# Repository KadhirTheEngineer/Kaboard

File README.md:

# Kaboard

An ultra-low profile 36-key wireless split keyboard with the Seeed XIAO nrf52840 dev board. Low power and insane battery life. 

Based on the chocofi and wireless corne.

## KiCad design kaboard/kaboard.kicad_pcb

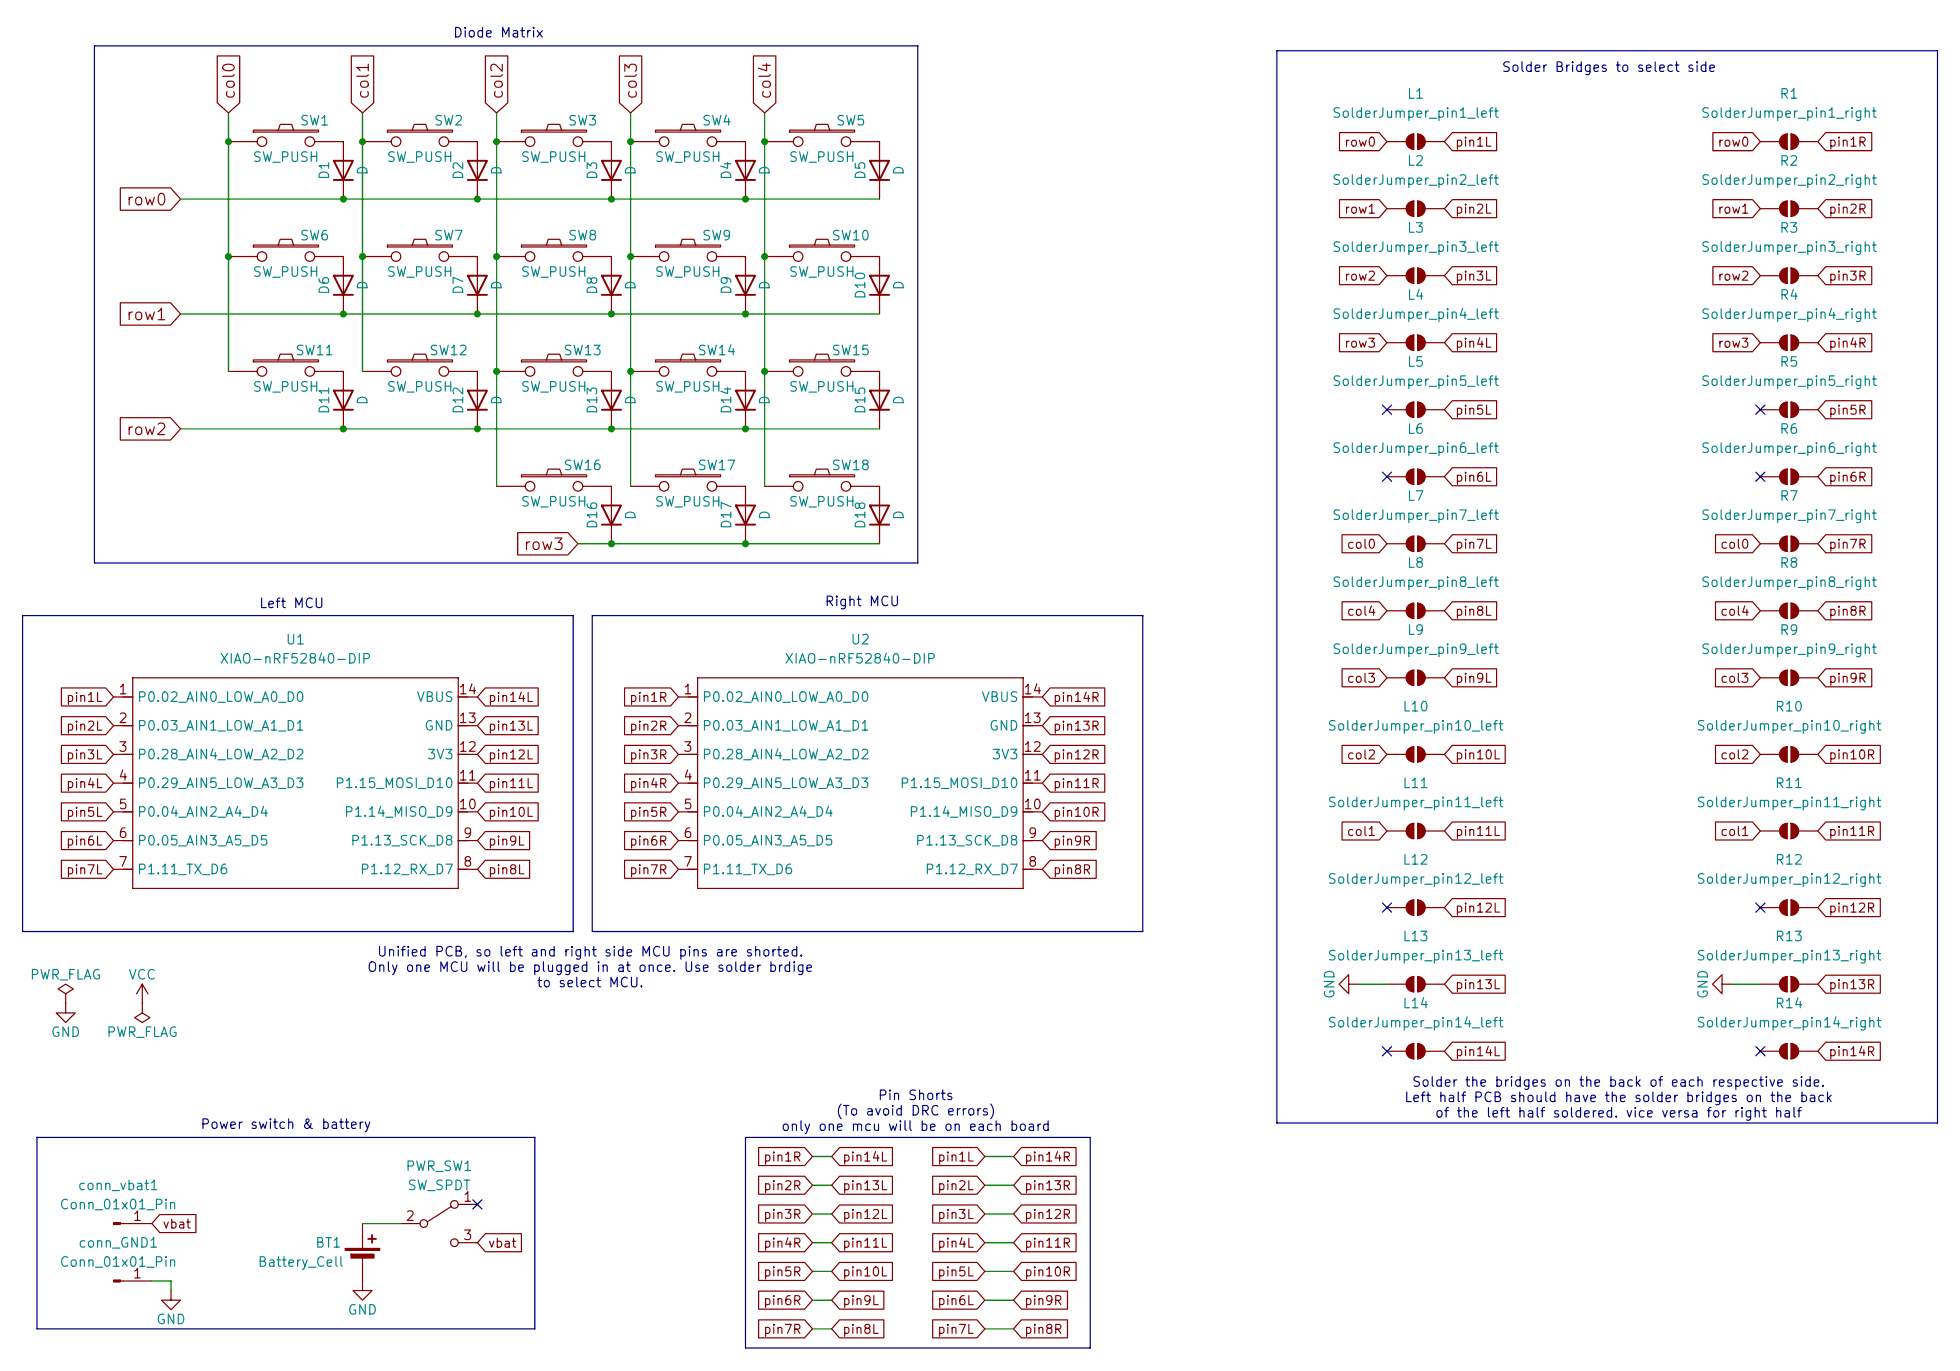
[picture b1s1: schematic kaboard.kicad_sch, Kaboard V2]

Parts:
BT1: Battery_Cell; Battery_pads_reversible
D1, D2, D3, D4, D5, D6, D7, D8, D9, D10, D11, D12, D13, D14, D15, D16, D17, D18: D; D_SMD_TH
L1: SolderJumper_pin1_left; SolderJumper-2_P1.3mm_Open_TrianglePad1.0x1.5mm
L2: SolderJumper_pin2_left; SolderJumper-2_P1.3mm_Open_TrianglePad1.0x1.5mm
L3: SolderJumper_pin3_left; SolderJumper-2_P1.3mm_Open_TrianglePad1.0x1.5mm
L4: SolderJumper_pin4_left; SolderJumper-2_P1.3mm_Open_TrianglePad1.0x1.5mm
L5: SolderJumper_pin5_left; SolderJumper-2_P1.3mm_Open_TrianglePad1.0x1.5mm
L6: SolderJumper_pin6_left; SolderJumper-2_P1.3mm_Open_TrianglePad1.0x1.5mm
L7: SolderJumper_pin7_left; SolderJumper-2_P1.3mm_Open_TrianglePad1.0x1.5mm
L8: SolderJumper_pin8_left; SolderJumper-2_P1.3mm_Open_TrianglePad1.0x1.5mm
L9: SolderJumper_pin9_left; SolderJumper-2_P1.3mm_Open_TrianglePad1.0x1.5mm
L10: SolderJumper_pin10_left; SolderJumper-2_P1.3mm_Open_TrianglePad1.0x1.5mm
L11: SolderJumper_pin11_left; SolderJumper-2_P1.3mm_Open_TrianglePad1.0x1.5mm
L12: SolderJumper_pin12_left; SolderJumper-2_P1.3mm_Open_TrianglePad1.0x1.5mm
L13: SolderJumper_pin13_left; SolderJumper-2_P1.3mm_Open_TrianglePad1.0x1.5mm
L14: SolderJumper_pin14_left; SolderJumper-2_P1.3mm_Open_TrianglePad1.0x1.5mm
PWR_SW1: SW_SPDT; power_switch_padreverse
R1: SolderJumper_pin1_right; SolderJumper-2_P1.3mm_Open_TrianglePad1.0x1.5mm
R2: SolderJumper_pin2_right; SolderJumper-2_P1.3mm_Open_TrianglePad1.0x1.5mm
R3: SolderJumper_pin3_right; SolderJumper-2_P1.3mm_Open_TrianglePad1.0x1.5mm
R4: SolderJumper_pin4_right; SolderJumper-2_P1.3mm_Open_TrianglePad1.0x1.5mm
R5: SolderJumper_pin5_right; SolderJumper-2_P1.3mm_Open_TrianglePad1.0x1.5mm
R6: SolderJumper_pin6_right; SolderJumper-2_P1.3mm_Open_TrianglePad1.0x1.5mm
R7: SolderJumper_pin7_right; SolderJumper-2_P1.3mm_Open_TrianglePad1.0x1.5mm
R8: SolderJumper_pin8_right; SolderJumper-2_P1.3mm_Open_TrianglePad1.0x1.5mm
R9: SolderJumper_pin9_right; SolderJumper-2_P1.3mm_Open_TrianglePad1.0x1.5mm
R10: SolderJumper_pin10_right; SolderJumper-2_P1.3mm_Open_TrianglePad1.0x1.5mm
R11: SolderJumper_pin11_right; SolderJumper-2_P1.3mm_Open_TrianglePad1.0x1.5mm
R12: SolderJumper_pin12_right; SolderJumper-2_P1.3mm_Open_TrianglePad1.0x1.5mm
R13: SolderJumper_pin13_right; SolderJumper-2_P1.3mm_Open_TrianglePad1.0x1.5mm
R14: SolderJumper_pin14_right; SolderJumper-2_P1.3mm_Open_TrianglePad1.0x1.5mm
SW1, SW2, SW3, SW4, SW5, SW6, SW7, SW8, SW9, SW10, SW11, SW12, SW13, SW14, SW15, SW16, SW17, SW18: SW_PUSH; Kailh_socket_PG1350_reversible
U1, U2: XIAO-nRF52840-DIP
conn_GND1: Conn_01x01_Pin; PinHeader_1x01_P1.00mm_Horizontal
conn_vbat1: Conn_01x01_Pin; PinHeader_1x01_P1.00mm_Horizontal

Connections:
GND: BT1.2 (-), L13.1 (A), R13.1 (A), conn_GND1.1
unnamed: BT1.1 (+), PWR_SW1.2 (B)
unnamed: D1.2 (A), SW1.2
unnamed: D2.2 (A), SW2.2
unnamed: D3.2 (A), SW3.2
unnamed: D4.2 (A), SW4.2
unnamed: D5.2 (A), SW5.2
unnamed: D6.2 (A), SW6.2
unnamed: D7.2 (A), SW7.2
unnamed: D8.2 (A), SW8.2
unnamed: D9.2 (A), SW9.2
unnamed: D10.2 (A), SW10.2
unnamed: D11.2 (A), SW11.2
unnamed: D12.2 (A), SW12.2
unnamed: D13.2 (A), SW13.2
unnamed: D14.2 (A), SW14.2
unnamed: D15.2 (A), SW15.2
unnamed: D16.2 (A), SW16.2
unnamed: D17.2 (A), SW17.2
unnamed: D18.2 (A), SW18.2
col0: L7.1 (A), R7.1 (A), SW1.1, SW6.1, SW11.1
col1: L11.1 (A), R11.1 (A), SW2.1, SW7.1, SW12.1
col2: L10.1 (A), R10.1 (A), SW3.1, SW8.1, SW13.1, SW16.1
col3: L9.1 (A), R9.1 (A), SW4.1, SW9.1, SW14.1, SW17.1
col4: L8.1 (A), R8.1 (A), SW5.1, SW10.1, SW15.1, SW18.1
pin6L: L6.2 (B), R9.2 (B), U1.6 (P0.05_AIN3_A5_D5), U2.9 (P1.13_SCK_D8)
pin6R: L9.2 (B), R6.2 (B), U1.9 (P1.13_SCK_D8), U2.6 (P0.05_AIN3_A5_D5)
pin7L: L7.2 (B), R8.2 (B), U1.7 (P1.11_TX_D6), U2.8 (P1.12_RX_D7)
pin7R: L8.2 (B), R7.2 (B), U1.8 (P1.12_RX_D7), U2.7 (P1.11_TX_D6)
pin10L: L10.2 (B), R5.2 (B), U1.10 (P1.14_MISO_D9), U2.5 (P0.04_AIN2_A4_D4)
pin10R: L5.2 (B), R10.2 (B), U1.5 (P0.04_AIN2_A4_D4), U2.10 (P1.14_MISO_D9)
pin11L: L11.2 (B), R4.2 (B), U1.11 (P1.15_MOSI_D10), U2.4 (P0.29_AIN5_LOW_A3_D3)
pin11R: L4.2 (B), R11.2 (B), U1.4 (P0.29_AIN5_LOW_A3_D3), U2.11 (P1.15_MOSI_D10)
pin12L: L12.2 (B), R3.2 (B), U1.12 (3V3), U2.3 (P0.28_AIN4_LOW_A2_D2)
pin12R: L3.2 (B), R12.2 (B), U1.3 (P0.28_AIN4_LOW_A2_D2), U2.12 (3V3)
pin13L: L13.2 (B), R2.2 (B), U1.13 (GND), U2.2 (P0.03_AIN1_LOW_A1_D1)
pin13R: L2.2 (B), R13.2 (B), U1.2 (P0.03_AIN1_LOW_A1_D1), U2.13 (GND)
pin14L: L14.2 (B), R1.2 (B), U1.14 (VBUS), U2.1 (P0.02_AIN0_LOW_A0_D0)
pin14R: L1.2 (B), R14.2 (B), U1.1 (P0.02_AIN0_LOW_A0_D0), U2.14 (VBUS)
row0: D1.1 (K), D2.1 (K), D3.1 (K), D4.1 (K), D5.1 (K), L1.1 (A), R1.1 (A)
row1: D6.1 (K), D7.1 (K), D8.1 (K), D9.1 (K), D10.1 (K), L2.1 (A), R2.1 (A)
row2: D11.1 (K), D12.1 (K), D13.1 (K), D14.1 (K), D15.1 (K), L3.1 (A), R3.1 (A)
row3: D16.1 (K), D17.1 (K), D18.1 (K), L4.1 (A), R4.1 (A)
vbat: PWR_SW1.3 (C), conn_vbat1.1

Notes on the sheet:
Solder Bridges to select side
Solder the bridges on the back of each respective side. Left half PCB should have the solder bridges on the back of the left half soldered. vice versa for right half
Diode Matrix
Left MCU
Unified PCB, so left and right side MCU pins are shorted. Only one MCU will be plugged in at once. Use solder brdige to select MCU.
Pin Shorts (To avoid DRC errors) only one mcu will be on each board
Right MCU
Power switch & battery

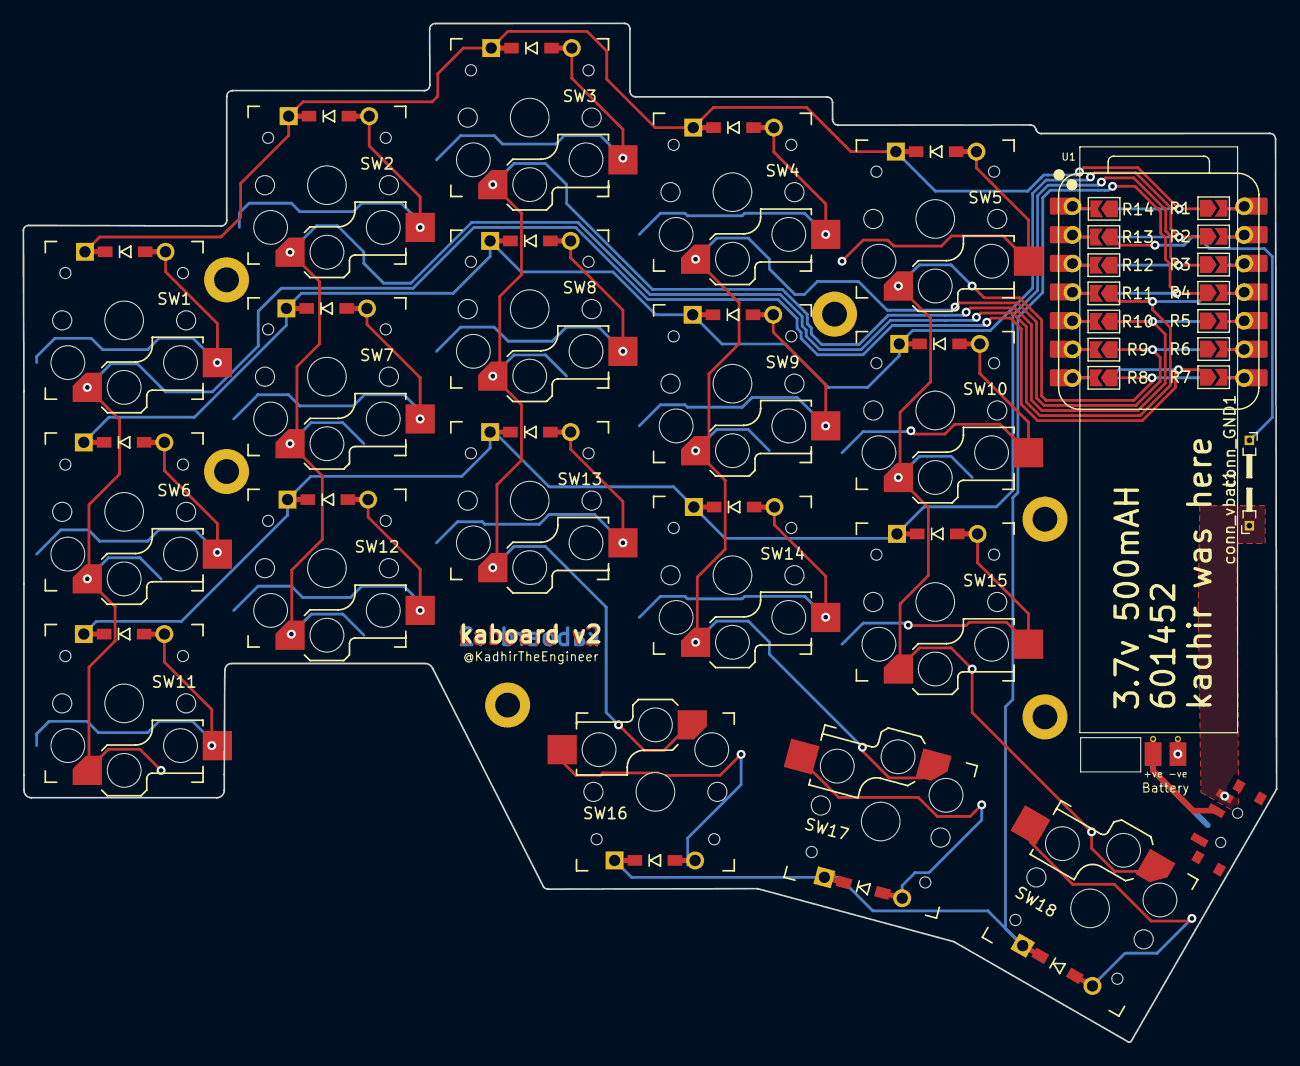
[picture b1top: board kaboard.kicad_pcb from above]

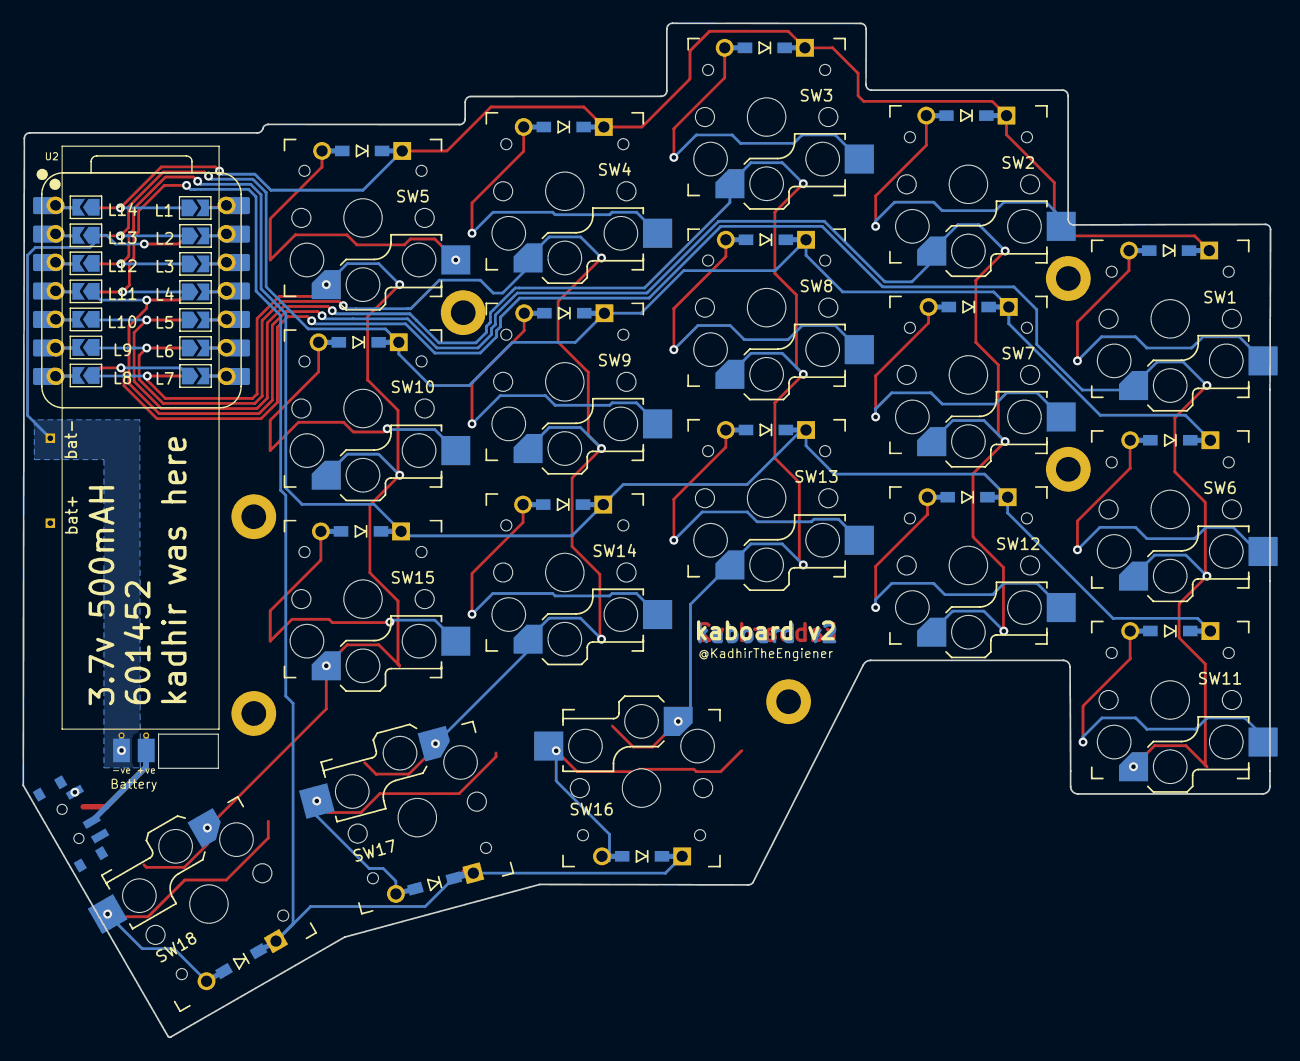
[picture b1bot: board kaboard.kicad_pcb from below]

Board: 2 copper layers, 111.3 x 90.4 mm, 76 parts (15 on the bottom side), 44 nets.

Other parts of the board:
h2: h2; LEGO_HOLE
h3: h3; LEGO_HOLE
h4: h4; LEGO_HOLE
h5: h5; LEGO_HOLE
h6: h6; LEGO_HOLE
h7: h7; LEGO_HOLE

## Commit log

2025-08-31 final
2025-09-02 mechanical stuff
2025-09-02 pcb updates
2025-09-02 case test
2025-09-03 battery test
2025-09-03 switchplate test
